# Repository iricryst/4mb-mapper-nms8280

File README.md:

# Philips NMS 8280 MSX2 4 MB Memory Mapper

A low-profile PCB implementation of the 4 MB memory mapper for the Philips NMS 8280 MSX2, based on the original design by Hans Oranje. The board is intended to replace the stock memory while keeping the mapper at slot 3.2, with the required connections and piggybacking arranged on the PCB instead of a large wiring harness.
<br>
<br>

## Contents

- [Design files](#design-files)
- [Bill of materials](#bill-of-materials)
- [Manual](#manual)
- [Result & test](#result--test)
- [Issues](#issues)
- [References and datasheets](#references-and-datasheets)

<br>
<br>

## Design files

- [KICAD](./KICAD/) 
- [Gerber files](./gerber/)
<br>
<br>

## Bill of materials

Use LS or HCT logic IC's.\
Use rounded narrow 2,54 mm pin headers\
Use stamped leaf spring dip socket, with the square holes\
  Use above combination to overcome slight misallignment of the pins against the sockets on the mainboard.\
  I didn't have the exact measurements documented. And even with a caliper measurements tend be inaccurate.  

Parts not described in the interactive BOM.
| Part | Amount  |
| --- | --- |
| 2x9 2,54mm DIP Socket stamped leaf spring | 2 |
| 2x8 2,54mm DIP Socket stamped leaf spring | 2 |
| 2x7 2,54mm DIP Socket stamped leaf spring | 1 |
| 1x50 2,54mm Rounded precision pin headers | 2 |

The Hyundai RAM used by this design is just wat I found in my drawer. It came of a 16 MB 72pins FPM module. 
Any 4Mx4 DRAM / FPM layout will work. I used 60ns against the 120ns original RAM without, any problems.
<br>

- [Main PCB interactive BOM](./KICAD/bom/ibom.html)
- [All-SMD PCB interactive BOM](./kicad_alll_smd/bom/ibom.html)
<br>

<br>
<br>

## Manual

Use the cutout image as a reference for component locations. The J1 wiring points are marked with a red dot and the corresponding wire number.

### Prepare the mainboard

- Remove the memory ICs IC133, IC134, IC135, and IC136, and replace them with DIP sockets. Only IC133 and IC134 require sockets, but socketing all original memory locations is recommended in case you need to restore the stock configuration.
- Remove logic ICs IC147, IC149, and IC131, and replace them with DIP sockets.
- Remove R127 and R128 (100 ohms). They are located at the red X marks in the image.

<br>
<br>

### Prepare the drop-in 4 MB PCB

- Assemble all SMD components.
- Cut the required rounded pins to size for CONN133, CONN134, CONN147, CONN149, and CONN131.
- **Do not solder the pins to the board yet.**
<br>
<br>

### Test-fit on the mainboard

- Fit the rounded pins into the corresponding sockets on the mainboard.
- Fit the drop-in PCB over the pins on the corresponding connectors and sockets. Although measurements were taken twice after prototyping, a slight offset remains. Larger sockets and smaller rounded pins provide some room for error.
- When all pins are in place and the PCB is straight and level, tack the outermost pins at the corners of the sockets to hold them in place. Keep heating time as short as possible.
- Remove the PCB with the partially soldered pins from the mainboard.
- Finish soldering the remaining pins, then solder IC149 and IC149B1.
<br>
<br>

### Connector J1 wiring

Use 30 AWG wire, or strip a floppy-disk/IDE ribbon cable.

| J1 pin | Connect to |
| --- | --- |
| J1 | IC180 pin 12 |
| J2 | R130, left leg when facing the mainboard as shown in the cutout image |
| J3 | IC111 pin 11 |
| J4 | R127, left pinhole when facing the mainboard as shown in the cutout image |
| J5 | R128, left pinhole when facing the mainboard as shown in the cutout image |
| J6 | IC161 pin 11 |
| J7 | IC176 pin 11 |
| J8 | IC176 pin 13 |
| J9 | IC178 pin 5 |
| J10 | IC178 pin 7 |
<br>
<br>

## Result & test

Plug in the finished PCB, carefully arranging the wires so they do not get trapped between the pin headers and DIP sockets. Power on the computer. With the stock ROM, the boot screen should report 128 KB of user RAM. Run a RAM checker to verify all 4096 KB.

<br>
<br>

## Issues

- The 1 mm connector J1 footprint is small for comfortable hand soldering.
- Silkscreen text could be a few pixels larger.
<br>
<br>

## References and datasheets

- [Hans Oranje's original 4 MB mapper paper (Dutch)](./doc/4mbnms8280.pdf)
- [Philips NMS 8280 service manual](./doc/nms8280_service_manual.pdf)
- [HY5117404B RAM datasheet](./doc/HY5117404B.pdf)
- [SN74LS00 datasheet](./doc/SN74LS00.pdf)
- [SN74LS08 datasheet](./doc/SN74LS08.pdf)
- [SN74LS125 datasheet](./doc/SN74LS125.pdf)
- [SN74LS157 datasheet](./doc/SN74LS157.pdf)
- [SN74LS670 datasheet](./doc/SN74LS670.pdf)

The RAM is an HY5117404B, represented by the custom `HYB5117400BJ` symbol in the schematic. The custom `1464` symbol does not identify a manufacturer part number, so its exact component cannot be determined from the schematic alone.

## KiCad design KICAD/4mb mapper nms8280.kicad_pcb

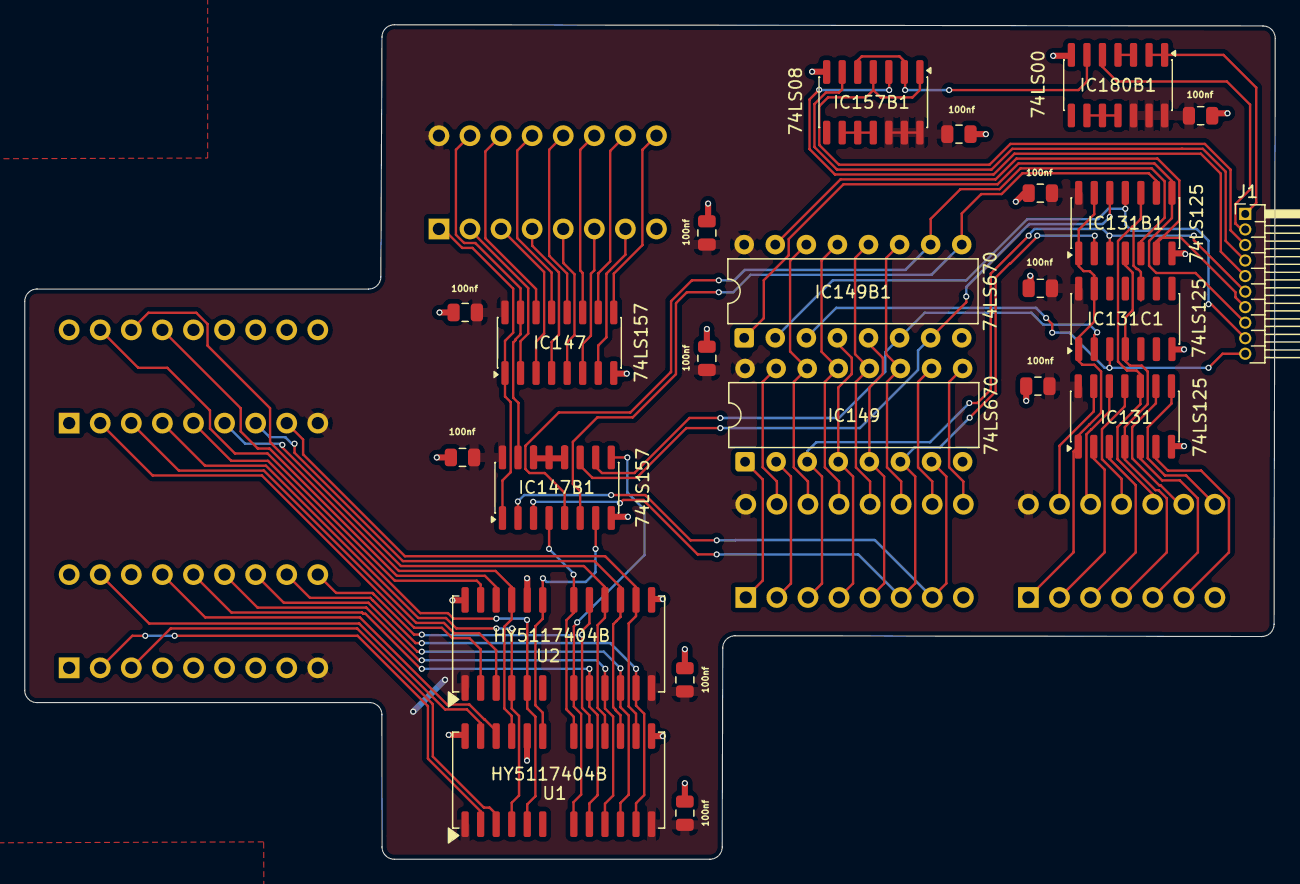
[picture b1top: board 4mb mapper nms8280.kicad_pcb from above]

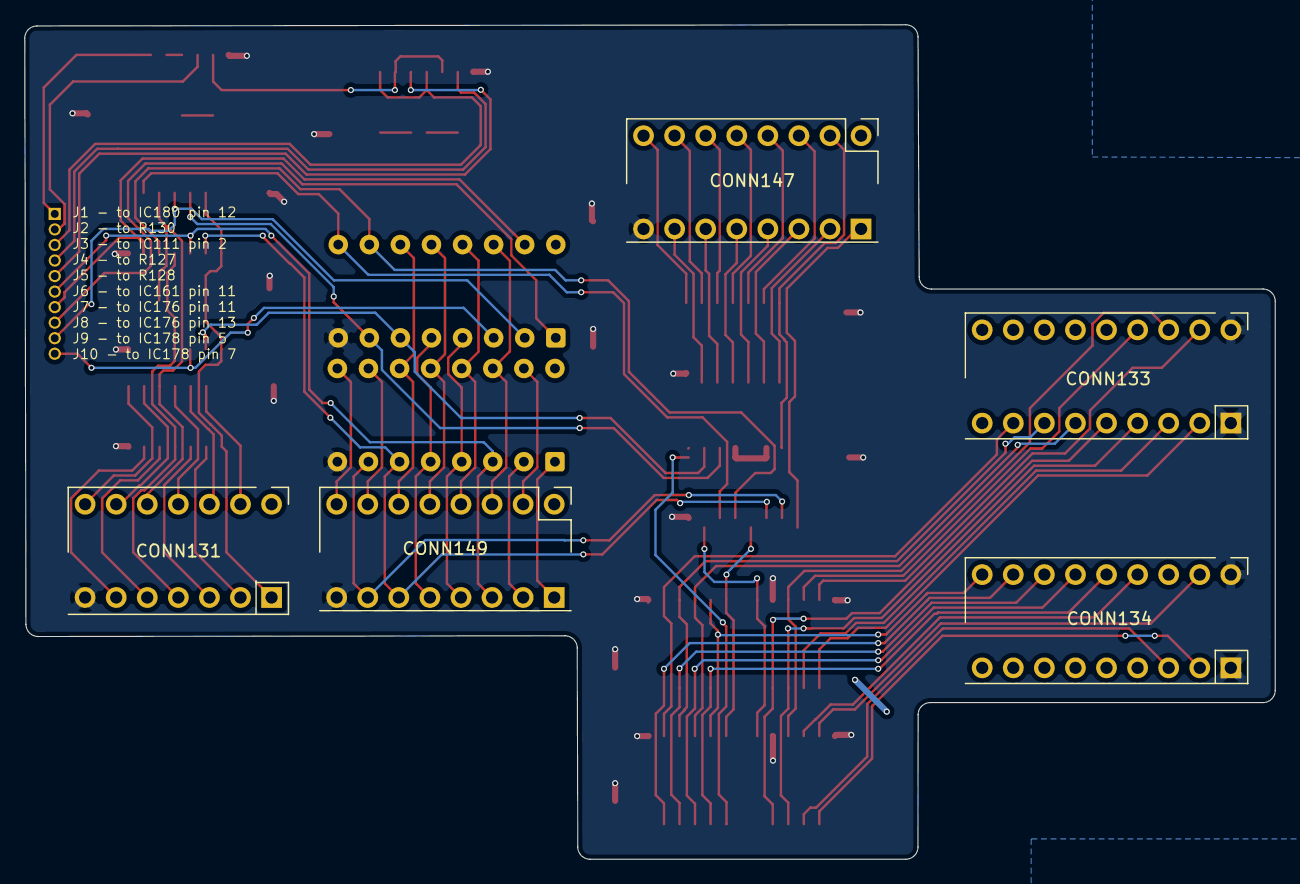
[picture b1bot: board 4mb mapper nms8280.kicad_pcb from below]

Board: 2 copper layers, 102.2 x 68.2 mm, 28 parts (5 on the bottom side), 82 nets.

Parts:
C1, C2, C131, C131B1, C131B2, C147, C147B1, C149, C149B1, C157B1, C180B1: 100nf; C_0805_2012Metric
CONN131: Pin Header 2x7 2,54mm Rounded; PinHeader_2x07_P2.54mm_Vertical
CONN133, CONN134: Pin Header 2x9 2,54mm Rounded; PinHeader_2x09_P2.54mm_Vertical
CONN147, CONN149: Pin Header 2x8 2,54mm Rounded; PinHeader_2x08_P2.54mm_Vertical
IC131, IC131B1, IC131C1: 74LS125; SOIC-14_3.9x8.7mm_P1.27mm
IC147, IC147B1: 74LS157; SOIC-16_3.9x9.9mm_P1.27mm
IC149, IC149B1: 74LS670; DIP-16_W7.62mm
IC157B1: 74LS08; SOIC-14_3.9x8.7mm_P1.27mm
IC180B1: 74LS00; SOIC-14_3.9x8.7mm_P1.27mm
J1: Conn_01x10_Pin; PinHeader_1x10_P1.27mm_Horizontal
U1, U2: HY5117404B; SOJ-2624_7.62x18.415mm_P1.27mm

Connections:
/4mb mapper nms8280/131b_131c_p13: CONN131.1 (1A), IC131.1 (1E), IC131B1.1 (1E), IC131B1.13 (4E), IC131C1.1 (1E), IC131C1.13 (4E)
/4mb mapper nms8280/<NO NET>: IC180B1.1 (1A), IC180B1.2 (1B), J1.1
/4mb mapper nms8280/IC131_P2: CONN131.2 (1B), IC131.2 (1D)
/4mb mapper nms8280/IC131_P3: CONN131.3 (1Y), IC131.3 (1O)
/4mb mapper nms8280/IC131_P4_IC131B: CONN131.4 (2A), IC131.4 (2E), IC131B1.4 (2E), IC131C1.4 (2E)
/4mb mapper nms8280/IC131_P5: CONN131.5 (2B), IC131.5 (2D)
/4mb mapper nms8280/IC131_P6: CONN131.6 (2Y), IC131.6 (2O)
/4mb mapper nms8280/IC131_P8: CONN131.8 (3Y), IC131.8 (3O)
/4mb mapper nms8280/IC131_P9: CONN131.9 (3A), IC131.9 (3D)
/4mb mapper nms8280/IC131_P10_IC131B: CONN131.10 (3B), IC131.10 (3E), IC131B1.10 (3E), IC131C1.10 (3E)
/4mb mapper nms8280/IC131_P11: CONN131.11 (4Y), IC131.11 (4O)
/4mb mapper nms8280/IC131_P12: CONN131.12 (4A), IC131.12 (4D)
/4mb mapper nms8280/IC131_P13: CONN131.13 (4B), IC131.13 (4E)
/4mb mapper nms8280/IC147_P1_IC147B: CONN147.1 (S), IC147.1 (S), IC147B1.1 (S)
/4mb mapper nms8280/IC147_P2: CONN147.2 (A0), IC147.2 (I0a)
/4mb mapper nms8280/IC147_P3: CONN147.3 (B0), IC147.3 (I1a)
/4mb mapper nms8280/IC147_P4: CONN147.4 (Y0), IC147.4 (Za)
/4mb mapper nms8280/IC147_P5: CONN147.5 (A1), IC147.5 (I0b)
/4mb mapper nms8280/IC147_P6: CONN147.6 (B1), IC147.6 (I1b)
/4mb mapper nms8280/IC147_P7: CONN147.7 (Y1), IC147.7 (Zb)
/4mb mapper nms8280/IC147_P9: CONN147.9 (Y2), IC147.9 (Zc)
/4mb mapper nms8280/IC147_P10: CONN147.10 (B2), IC147.10 (I1c)
/4mb mapper nms8280/IC147_P11: CONN147.11 (A2), IC147.11 (I0c)
/4mb mapper nms8280/IC147_P12: CONN147.12 (Y3), IC147.12 (Zd)
/4mb mapper nms8280/IC147_P13: CONN147.13 (B3), IC147.13 (I1d)
/4mb mapper nms8280/IC147_P14: CONN147.14 (A3), IC147.14 (I0d)
/4mb mapper nms8280/IC147_P15_IC147B: CONN147.15 (E), IC147.15 (E), IC147B1.15 (E)
/4mb mapper nms8280/IC149_P1: CONN149.1 (D2), IC149.1 (D2)
/4mb mapper nms8280/IC149_P2: CONN149.2 (D3), IC149.2 (D3)
/4mb mapper nms8280/IC149_P3: CONN149.3 (D4), IC131B1.3 (1O), IC149.3 (D4), J1.6
/4mb mapper nms8280/IC149_P4_IC149B: CONN149.4 (RB), IC149.4 (Rb), IC149B1.4 (Rb)
/4mb mapper nms8280/IC149_P5_IC149B: CONN149.5 (RA), IC149.5 (Ra), IC149B1.5 (Ra)
/4mb mapper nms8280/IC149_P6: CONN149.6 (Q4), IC131B1.2 (1D), IC147B1.3 (I1a), IC149.6 (Q4)
/4mb mapper nms8280/IC149_P7: CONN149.7 (Q3), IC147B1.2 (I0a), IC149.7 (Q3)
/4mb mapper nms8280/IC149_P9: CONN149.9 (Q2), IC149.9 (Q2)
/4mb mapper nms8280/IC149_P10: CONN149.10 (Q1), IC149.10 (Q1)
/4mb mapper nms8280/IC149_P11_IC149B: CONN149.11 (ER), IC149.11 (~Er), IC149B1.11 (~Er)
/4mb mapper nms8280/IC149_P12_IC149B: CONN149.12 (EW), IC149.12 (~Ew), IC149B1.12 (~Ew)
/4mb mapper nms8280/IC149_P13_IC149B: CONN149.13 (WB), IC149.13 (Wb), IC149B1.13 (Wb)
/4mb mapper nms8280/IC149_P14_IC149B: CONN149.14 (WA), IC149.14 (Wa), IC149B1.14 (Wa)
/4mb mapper nms8280/IC149_P15: CONN149.15 (D1), IC149.15 (D1)
/ram section/A0_IC133/134_P14: CONN134.14 (A0), U1.9 (A0), U2.9 (A0)
/ram section/A1_IC133/134_P13: CONN134.13 (A1), U1.10 (A1), U2.10 (A1)
/ram section/A2_IC133/134_P12: CONN134.12 (A2), U1.11 (A2), U2.11 (A2)
/ram section/A3_IC133/134_P11: CONN134.11 (A3), U1.12 (A3), U2.12 (A3)
/ram section/A4_IC133/134_P8: CONN133.8 (A4), U1.15 (A4), U2.15 (A4)
/ram section/A5_IC133/134_P7: CONN133.7 (A5), U1.16 (A5), U2.16 (A5)
/ram section/A6_IC133/134_P6: CONN133.6 (A6), U1.17 (A6), U2.17 (A6)
/ram section/A7_IC133/134_P10: CONN134.10 (A7), U1.18 (A7), U2.18 (A7)
/ram section/CAS_IC133/134_P16: CONN133.16 (CAS), U1.23 (CAS), U2.23 (CAS)
/ram section/D0_IC134_P2: CONN134.2 (D0), U1.2 (D0)
/ram section/D1_IC134_P3: CONN134.3 (D1), U1.3 (D1)
/ram section/D2_IC134_P15: CONN134.15 (D2), U1.24 (D2)
/ram section/D3_IC134_P17: CONN134.17 (D3), U1.25 (D3)
/ram section/D4_IC133_P2: CONN133.2 (D0), U2.2 (D0)
/ram section/D5_IC133_P3: CONN133.3 (D1), U2.3 (D1)
/ram section/D6_IC133_P15: CONN133.15 (D2), U2.24 (D2)
/ram section/D7_IC133_P17: CONN133.17 (D3), U2.25 (D3)
/ram section/RAS_IC133_P5: CONN133.5 (RAS), U1.5 (RAS), U2.5 (RAS)
/ram section/WE_IC133_P4: CONN133.4 (WE), U1.4 (WE), U2.4 (WE)
A8_IC147B_P4: IC147B1.4 (Za), U1.19 (A8), U2.19 (A8)
A9_IC147B_P7: IC147B1.7 (Zb), U1.21 (A9), U2.21 (A9)
A10_IC147B_P7: IC147B1.9 (Zc), U1.8 (A10), U2.8 (A10)
GND: C1.2, C2.2, C131.2, C131B1.2, C131B2.2, C147.1, C147B1.1, C149.2, C149B1.2, C157B1.1, C180B1.1, CONN131.7 (GND), CONN133.1 (OE), CONN133.18 (GND), CONN134.1 (OE), CONN134.18 (GND), CONN147.8 (GND), CONN149.8 (GND), IC131.7 (GND), IC131B1.7 (GND), IC131C1.7 (GND), IC147.8 (GND), IC147B1.8 (GND), IC149.8 (GND), IC149B1.8 (GND), IC157B1.7 (GND), IC180B1.7 (GND), U1.14 (GND), U1.22 (OE), U1.26 (GND), U2.14 (GND), U2.22 (OE), U2.26 (GND)
unnamed: IC131B1.5 (2D), IC147B1.5 (I0b), IC149B1.10 (Q1)
unnamed: IC131B1.6 (2O), IC149B1.15 (D1), J1.7
unnamed: IC131B1.9 (3D), IC147B1.6 (I1b), IC149B1.9 (Q2)
unnamed: IC131B1.8 (3O), IC149B1.1 (D2), J1.8
unnamed: IC131B1.12 (4D), IC147B1.11 (I0c), IC149B1.7 (Q3)
unnamed: IC131B1.11 (4O), IC149B1.2 (D3), J1.9
unnamed: IC131C1.2 (1D), IC147B1.10 (I1c), IC149B1.6 (Q4)
unnamed: IC131C1.3 (1O), IC149B1.3 (D4), J1.10
unnamed: IC147B1.12 (Zd), IC147B1.13 (I1d), IC147B1.14 (I0d)
unnamed: IC157B1.1 (1A), IC157B1.4 (2A), J1.3
unnamed: IC157B1.2 (1B), IC157B1.5 (2B), IC180B1.6 (2Y)
unnamed: IC157B1.3 (1Y), J1.5
unnamed: IC157B1.6 (2Y), J1.4
unnamed: IC157B1.9 (3A), IC157B1.10 (3B), IC157B1.11 (4Y)
unnamed: IC180B1.3 (1Y), IC180B1.4 (2A)
unnamed: IC180B1.5 (2B), J1.2
unnamed: IC180B1.9 (3A), IC180B1.10 (3B), IC180B1.11 (4Y)
Vcc: C1.1, C2.1, C131.1, C131B1.1, C131B2.1, C147.2, C147B1.2, C149.1, C149B1.1, C157B1.2, C180B1.2, CONN131.14 (Vcc), CONN133.9 (Vcc), CONN134.9 (Vcc), CONN147.16 (Vcc), CONN149.16 (Vcc), IC131.14 (Vcc), IC131B1.14 (Vcc), IC131C1.14 (Vcc), IC147.16 (VCC), IC147B1.16 (VCC), IC149.16 (VCC), IC149B1.16 (VCC), IC157B1.12 (4A), IC157B1.13 (4B), IC157B1.14 (Vcc), IC180B1.12 (4A), IC180B1.13 (4B), IC180B1.14 (Vcc), U1.1 (Vcc), U1.13 (Vcc), U2.1 (Vcc), U2.13 (Vcc)
